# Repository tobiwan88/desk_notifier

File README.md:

# Desk notifier

A small desk display on an ESP32-S3. A round 240x240 GC9A01 screen turns through three animated pages: a clock with today's forecast for Munich, a cute squirrel that shows the indoor air quality from a BME688 sensor, and the squirrel's day at home, which follows the clock (coffee in the morning, laptop, lunch, reading, sleep). When the air gets bad the squirrel stays on screen and asks you to open a window until you press a button.

It started as the esp_eyes project (animated eyes on two displays) and was cut down to one display. The git history keeps the old work.

## What is in this repo
One repo holds the whole product: firmware, the custom board and the 3D-printed case.

| Part | Where | State |
|---|---|---|
| Firmware (ESP-IDF v6.1, C++23, host-tested core) | [`firmware/`](firmware/), [`docs/`](docs/) | Runs on the ESP32-S3 custom board (`DESK_BOARD_NOTIFIER_V1`) with a GC9A01, a BME688 and an SHT40; flashed and checked on a real board (sensors, display, Bluetooth setup). |
| Board `notifier-v1` (KiCad 10, 4 layers, 50 x 36 mm, JLCPCB assembly) | [`hardware/`](hardware/README.md) | Generated, routed and gate-checked, fab package builds. **Not ordered yet**: human review in KiCad, JLC placement preview and the display pinout check are still open ([`ORDER.md`](hardware/notifier-v1/ORDER.md)). |
| Case (Fusion, 3D printed PLA, two parts, snap-fit) | [`hardware/mechanics/`](hardware/mechanics/README.md) | First model with print files and a fit coupon. **Never printed.** |
| Helper tools (page previews, clip preparation) | [`tools/`](tools/), [`clipprep/`](clipprep/) | Used by the checks. |

## Limitations
Please read these before building one.
- **ESP32-S3 only.** The board uses an ESP32-S3-WROOM-1-N8R2, because C61 and C5 modules had no stock at JLCPCB. The earlier ESP32-C61 breadboard setup is no longer built or tested. The case is still untested (below).
- **The case is untested.** No part of it has been printed. The display module has no 3D model, so the pocket, window and plug alignment rest on assumed dimensions (header 2.54 mm, pin row 3.0 mm above the PCB edge, glass centre 26.5 mm above it, PCB plus glass 5.74 mm). Print `display_dummy.stl` and `coupon_m1.stl` first and compare. The SHT40 height (1.0 mm) is also an assumption. The cover needs one support and the USB-C collar may sit about 0.7 mm short of the connector.
- **Display orientation is unconfirmed.** The image is mirrored on X by default (`DESK_LCD_MIRROR_X`); flip it in menuconfig if your panel shows it backwards. The pin order of the display module on the board's socket is also still to be checked against a real module.
- **The air score is not BSEC.** It is a simple estimate from humidity and gas resistance and needs a few minutes of warm-up. The sensor reads a little warm next to the board, so indoor temperature is slightly high.
- **No firmware security by default.** The HTTP API, the pet page and OTA are open unless you set a token (`auth token`), the connection is plain HTTP, and the device is meant for a trusted home network. Do not expose it to the internet.
- **Weather and time need the internet** (Open-Meteo, SNTP). Without it the clock stays unset and the weather items disappear. The place defaults to Munich (change it with `POST /api/weather` or `weather at <lat> <lon>`), holidays are Bavarian, and the texts are English.
- **Pictures are stored but not shown** yet, there is one display, and the project is tuned to a single 240x240 round panel at 10 frames per second on a chip without an FPU.
- **The hardware generators overwrite KiCad edits.** Change `hardware/gen/*.py`, not the KiCad files, then re-run the pipeline. The router needs tools that `hardware/tools/setup_tools.sh` downloads, and its result differs between runs.
- **Development on macOS.** The scripts and notes assume macOS and a local ESP-IDF install in `~/esp/esp-idf`.

## What works today
- Rotating pages with fades, 10 frames per second. See [docs/pages.md](docs/pages.md).
- Five mascots, one per board (`idf.py menuconfig` → Desk notifier → Mascot): the squirrel, or a bunny, a stag, a lucky cat with her dog, or a penguin. The new ones have a home page (clock and air level) and a day page that follows their owner's week, and dress for the weather. The squirrel's extras (pet page, hearts, shop, visitors, plant) are add-ons with their own switches. See [docs/mascots.md](docs/mascots.md).
  - Clock: time (set over the internet), date, indoor and outdoor temperature, today's low, high and chance of rain.
  - Air: a squirrel mascot whose mood shows the air level (very good, good, okay, bad), with temperature, humidity and score.
  - Day: the squirrel at its desk at home, doing what fits the time and weekday. The room's climate changes it (stuffy air: it yawns or opens the window; too warm, too cold, too dry, too humid; a sudden smell), so does the weather (umbrella, cocoa, thunder), and special days decorate the room (birthday, anniversary, Christmas, Advent, Halloween, Oktoberfest, ...). The real weather shows in the window, the real time on the wall clock. The scene is never random, but little things are: blinks, glances, a wave, a bird on the windowsill, a ladybug on the desk, a shooting star, a paper plane, a rare golden acorn. The moon shows its real phase, rainbows follow rain, a window-sill plant grows with good air day after day, and a wall calendar counts down to birthdays.
  - Pet page at `http://<device>.local/pet`: feed it, have a coffee break or a party together, pet it, play, water the plant, say good night, give it gifts. Daily visits grow a friendship (five heart levels, never lost) with more reactions and visitors, and squirrel coins for the shop (six things a day: hats, places, things for the room, friends, seasonal specials); the squirrel picks its own outfit.
- Bad-air alert: the air page stays on, snoozed for 15 minutes by the button or by `POST /api/ack`. Without an alert the button shows the next page.
- Web page at `http://<device>.local/` and a small HTTP API.
- Wi-Fi, over-the-air updates, and a serial console.
- Picture upload (the clip format from esp_eyes) is stored but not shown yet.

Planned: pictures that stay on screen until acknowledged, Bosch BSEC2 for a proper IAQ value.

## What you need
Dev setup (works today), or the custom board in `hardware/` once it is built:
- ESP32-S3 board with 8 MB flash and PSRAM (the notifier-v1 board, or an S3 dev board with the same pins)
- GC9A01 round display, 240x240, SPI
- BME688 breakout (I2C)
- A push button (optional)
- USB cable

## The squirrel
The squirrel's mood follows the indoor air quality. What it wears follows the weather outside (Open-Meteo, Munich by default):

| Outside | Squirrel |
|---|---|
| below 8 °C | knitted hat and scarf |
| 25 °C or more | ice cream |
| sunny, daytime | sunglasses |
| drizzle, rain, thunder | umbrella |
| wind of 30 km/h or more | glides under the umbrella, tail streaming |

Items stack (cold, rainy and windy gives hat, umbrella and gliding). Preview every look on your computer with `uv run python tools/preview_pages.py out/` after `scripts/check.sh --quick`.

## Wiring
| Signal | GPIO | Note |
|---|---|---|
| Display SCL / SDA | 6 / 5 | |
| Display DC / RST / CS | 3 / 2 / 4 | |
| Display VCC / GND | 5V / GND | |
| BME688 SDA / SCL | 22 / 23 | 3V3, not 5V. Address 0x77 or 0x76, both are tried |
| Button | 24 | other leg to GND |

Details: [docs/wiring.md](docs/wiring.md). Pins can be changed in `idf.py menuconfig` under "Desk notifier".
If the picture is mirrored, flip `DESK_LCD_MIRROR_X` / `DESK_LCD_MIRROR_Y` there.

## Build and flash
You need ESP-IDF v6.1 and [uv](https://docs.astral.sh/uv/).

```sh
source scripts/idf-env.sh
cd firmware
idf.py -p /dev/cu.usbserial-XXXX flash monitor
```

## Connect to Wi-Fi
Open the serial console and run `wifi "<name>" <password>`. The device reboots and joins your network. It is then reachable as `desk-<last 6 MAC digits>.local`. The timezone is set in menuconfig (`DESK_TZ`, default Central Europe).

## API
By default the API needs no password (change with the console command `auth token`).

```sh
curl http://desk-xxxxxx.local/api/sensor     # temperature, humidity, pressure, gas, score
curl http://desk-xxxxxx.local/api/status     # uptime, memory, Wi-Fi, sensor state
curl -X POST http://desk-xxxxxx.local/api/ack   # snooze the alert
curl http://desk-xxxxxx.local/api/weather    # the last forecast
curl -X POST http://desk-xxxxxx.local/api/page -d '{"page":"day"}'   # clock, air, day or next ("weather" still works)
curl -X POST http://desk-xxxxxx.local/api/weather -d '{"lat":48.137,"lon":11.575,"place":"Munich"}'   # change the place
curl -X POST --data-binary @firmware.bin http://desk-xxxxxx.local/api/ota
```

## Console commands
`wifi`, `status`, `sensor`, `ack`, `page clock|air|day|next`, `weather [refresh | at <lat> <lon> [name]]`, `lcd pins`, `lcd init [hz]`, `hostname`, `auth open|token`, `token`, `reboot`, `factory-reset`.

## About the air-quality score
It is a simple estimate, not Bosch BSEC. 25 points come from humidity (best at 40 %) and 75 from the gas resistance compared with the highest value seen recently. It needs about 3 minutes to warm up and a stretch of clean air to be meaningful. The sensor also reads a little warm because it sits next to the board.

## For developers
`scripts/check.sh` runs the host tests (C++23, sanitizers), the Python tests and the firmware build. `--quick` skips the build. `uv run python tools/preview_pages.py` draws all pages as GIFs on your computer (after a host build). Pure logic lives in `firmware/components/*/core` and is tested on the PC. See [CLAUDE.md](CLAUDE.md) for the layout.

## Hardware and case
- Board: open `hardware/notifier-v1/notifier-v1.kicad_pro` with `hardware/open.sh`. Regenerate with `hardware/tools/pipeline_v1.sh`, check with `scripts/hw-check.sh`, order steps in [`hardware/notifier-v1/ORDER.md`](hardware/notifier-v1/ORDER.md), design notes in [`hardware/PLAN.md`](hardware/PLAN.md). Needs KiCad 10 (`source scripts/kicad-env.sh`).
- Case: print files and notes in [`hardware/mechanics/`](hardware/mechanics/README.md) (PLA, 0.2 mm layers, Bambu Lab plate included). Print the fit coupon first.
- Firmware: `idf.py build` in `firmware/` (target ESP32-S3). Wi-Fi, time zone and name can be set from a phone over Bluetooth: [`setup/`](setup/README.md).

## License
MIT. The BME68x driver in `firmware/components/sensor/third_party` is from Bosch Sensortec (BSD-3-Clause).

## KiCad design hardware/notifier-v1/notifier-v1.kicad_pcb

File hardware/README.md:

# Hardware: where to look

There is one KiCad project: **`notifier-v1/notifier-v1.kicad_pro`** (schematic + PCB).
Open it with `hardware/open.sh`, or File > Open Project in KiCad. Everything else is generated.

| What | Where |
|---|---|
| KiCad project (schematic, PCB) | `notifier-v1/` |
| Board profile (notes, rules the scripts check, datasheet cards) | `notifier-v1/BOARD.md`, `board.yaml`, `critical.yaml`, `parts/` |
| Order checklist, bring-up | `notifier-v1/ORDER.md` |
| Design notes, toolchain, lessons | `PLAN.md` |
| Review images (annotated renders, layers, 3D, schematic tiles) | `out/review/notifier-v1/` (after a pipeline run) |
| JLCPCB upload files (gerbers zip, BOM, CPL) | `out/fab/notifier-v1/` (after a pipeline run) |
| Router logs | `out/route/` |
| Board-neutral checks (critical blocks, regulator, impedance) | `calc/` (each takes the board folder) |
| Generators (edit these, not the KiCad files) | `gen/notifier_v1.py` (schematic), `gen/layout_v1.py` (placement) |

The KiCad files are regenerated by `tools/pipeline_v1.sh`: edits made in KiCad are overwritten on the
next run. Review in KiCad, then change the generators. `out/` is not in git; `tools/setup_tools.sh`
installs the routers once.

Agent skills (board-neutral): `hw-base` (read first), `kicad-schematic`, `kicad-layout`, `hw-parts` in `.claude/skills/`.

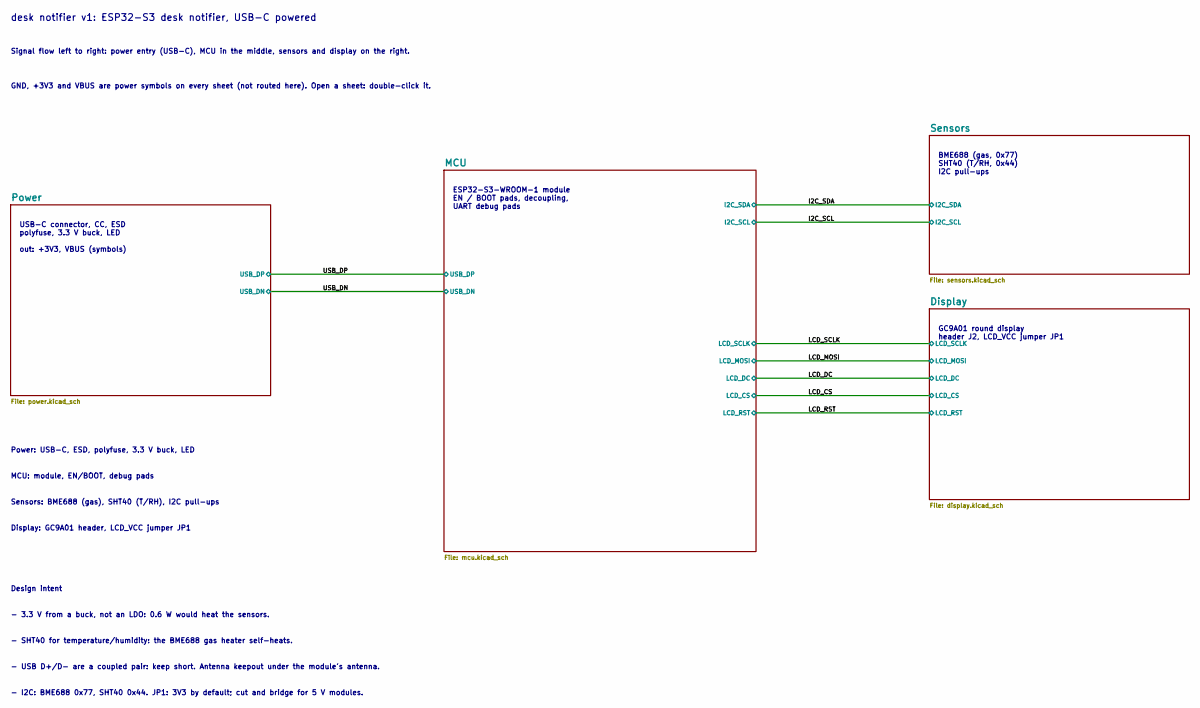
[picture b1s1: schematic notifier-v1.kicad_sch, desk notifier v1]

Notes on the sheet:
USB-C connector, CC, ESD polyfuse, 3.3 V buck, LED out: +3V3, VBUS (symbols)
ESP32-S3-WROOM-1 module EN / BOOT pads, decoupling, UART debug pads
Design intent
- 3.3 V from a buck, not an LDO: 0.6 W would heat the sensors.
MCU: module, EN/BOOT, debug pads
Power: USB-C, ESD, polyfuse, 3.3 V buck, LED
Signal flow left to right: power entry (USB-C), MCU in the middle, sensors and display on the right.
- USB D+/D- are a coupled pair: keep short. Antenna keepout under the module's antenna.
desk notifier v1: ESP32-S3 desk notifier, USB-C powered
GND, +3V3 and VBUS are power symbols on every sheet (not routed here). Open a sheet: double-click it.
- I2C: BME688 0x77, SHT40 0x44. JP1: 3V3 by default; cut and bridge for 5 V modules.
GC9A01 round display header J2, LCD_VCC jumper JP1
Display: GC9A01 header, LCD_VCC jumper JP1
BME688 (gas, 0x77) SHT40 (T/RH, 0x44) I2C pull-ups
Sensors: BME688 (gas), SHT40 (T/RH), I2C pull-ups
- SHT40 for temperature/humidity: the BME688 gas heater self-heats.

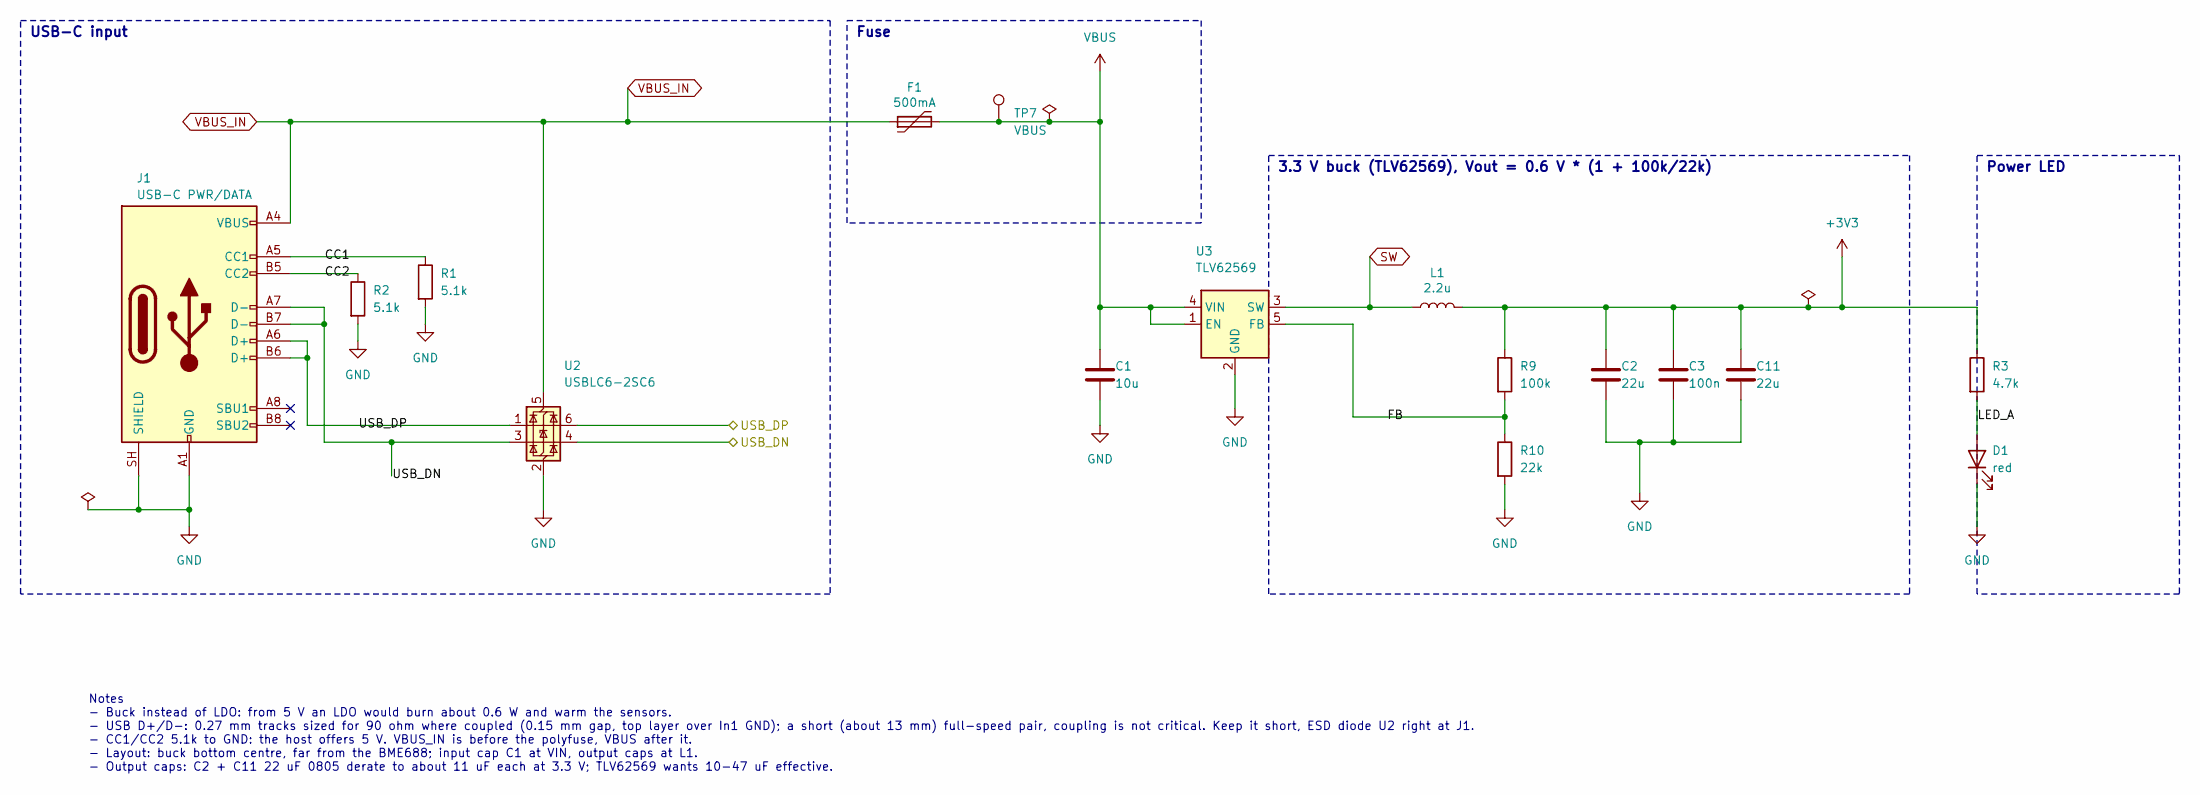
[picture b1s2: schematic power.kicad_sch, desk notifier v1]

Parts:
C1: 10u; C_0603_1608Metric; LCSC C19702
C2, C11: 22u; C_0805_2012Metric; LCSC C45783
C3: 100n; C_0402_1005Metric; LCSC C1525
D1: red; LED_0603_1608Metric; LCSC C2286
F1: 500mA; Fuse_1206_3216Metric; LCSC C70077
J1: USB-C PWR/DATA; USB_C_Receptacle_HRO_TYPE-C-31-M-12; LCSC C165948
L1: 2.2u; L_Cenker_CKCS4030; LCSC C354584
R1, R2: 5.1k; R_0402_1005Metric; LCSC C25905
R3: 4.7k; R_0402_1005Metric; LCSC C25900
R9: 100k; R_0402_1005Metric; LCSC C25741
R10: 22k; R_0402_1005Metric; LCSC C25768
TP7: VBUS; TestPoint_Pad_D1.0mm
U2: USBLC6-2SC6; SOT-23-6; LCSC C7519
U3: TLV62569; SOT-23-5; LCSC C141836

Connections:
+3V3: C2.1, C3.1, C11.1, L1.2, R3.1, R9.1; also elsewhere on the board
/Power/CC1: J1.A5 (CC1), R1.1
/Power/CC2: J1.B5 (CC2), R2.1
/Power/FB: R9.2, R10.1, U3.5 (FB)
/Power/LED_A: D1.2 (A), R3.2
/USB_DN: J1.A7 (D-), J1.B7 (D-), U2.3 (I/O2), U2.4 (I/O2); also elsewhere on the board
/USB_DP: J1.A6 (D+), J1.B6 (D+), U2.1 (I/O1), U2.6 (I/O1); also elsewhere on the board
GND: C1.2, C2.2, C3.2, C11.2, D1.1 (K), J1.A1 (GND), J1.A12 (GND), J1.B1 (GND), J1.B12 (GND), J1.SH (SHIELD), R1.2, R2.2, R10.2, U2.2 (GND), U3.2 (GND); also elsewhere on the board
SW: L1.1, U3.3 (SW)
VBUS: C1.1, F1.2, TP7.1, U3.1 (EN), U3.4 (VIN); also elsewhere on the board
VBUS_IN: F1.1, J1.A4 (VBUS), J1.A9 (VBUS), J1.B4 (VBUS), J1.B9 (VBUS), U2.5 (VBUS)

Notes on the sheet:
3.3 V buck (TLV62569), Vout = 0.6 V * (1 + 100k/22k)
USB-C input
Notes - Buck instead of LDO: from 5 V an LDO would burn about 0.6 W and warm the sensors. - USB D+/D-: 0.27 mm tracks sized for 90 ohm where coupled (0.15 mm gap, top layer over In1 GND); a short (about 13 mm) full-speed pair, coupling is not critical. Keep it short, ESD diode U2 right at J1. - CC1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
Power LED
Fuse

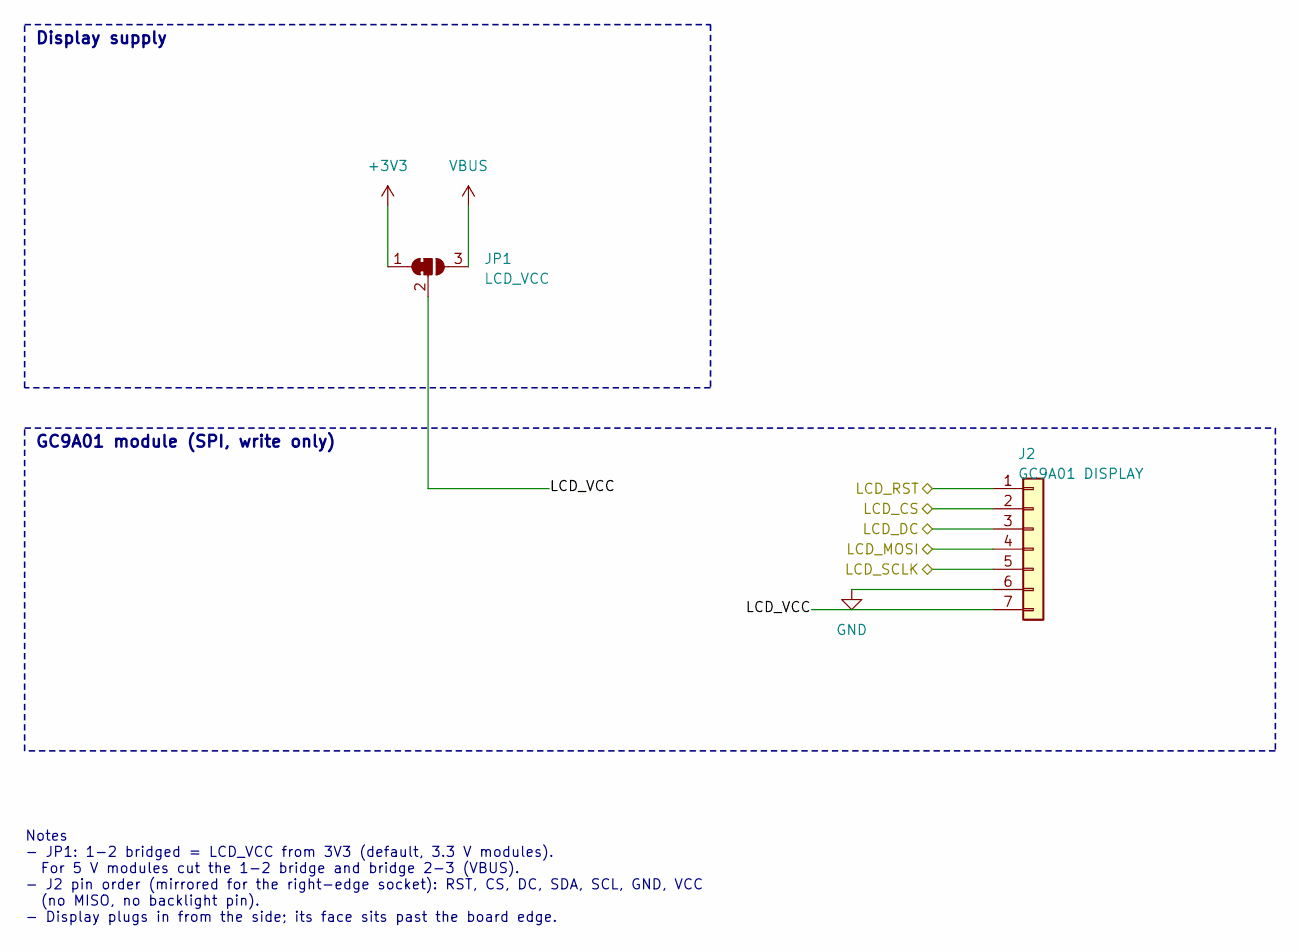
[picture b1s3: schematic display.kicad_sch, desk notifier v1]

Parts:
J2: GC9A01 DISPLAY; PinSocket_1x07_P2.54mm_Horizontal; LCSC C22436148
JP1: LCD_VCC; SolderJumper-3_P1.3mm_Bridged12_RoundedPad1.0x1.5mm

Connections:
+3V3: JP1.1 (A); also elsewhere on the board
/Display/LCD_VCC: J2.7, JP1.2 (C)
/LCD_CS: J2.2; also elsewhere on the board
/LCD_DC: J2.3; also elsewhere on the board
/LCD_MOSI: J2.4; also elsewhere on the board
/LCD_RST: J2.1; also elsewhere on the board
/LCD_SCLK: J2.5; also elsewhere on the board
GND: J2.6; also elsewhere on the board
VBUS: JP1.3 (B); also elsewhere on the board

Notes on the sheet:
Display supply
GC9A01 module (SPI, write only)
Notes - JP1: 1-2 bridged = LCD_VCC from 3V3 (default, 3.3 V modules). For 5 V modules cut the 1-2 bridge and bridge 2-3 (VBUS). - J2 pin order (mirrored for the right-edge socket): RST, CS, DC, SDA, SCL, GND, VCC (no MISO, no backlight pin). - Display plugs in from the side; its face sits past the 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

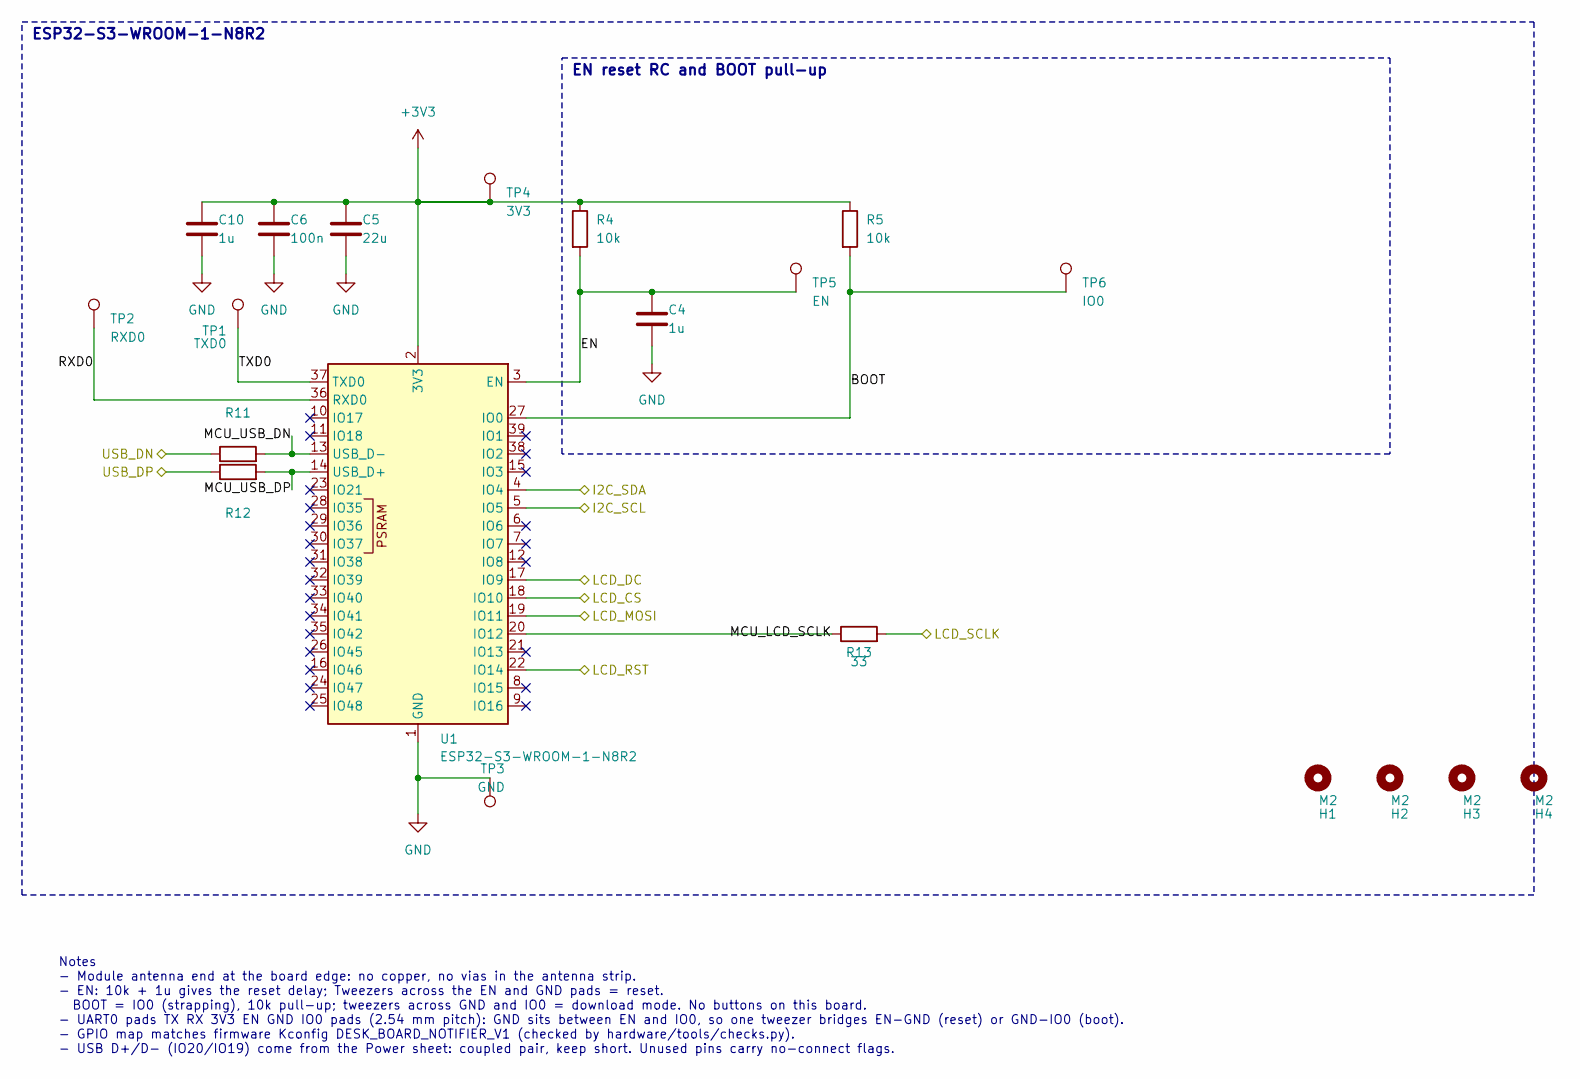
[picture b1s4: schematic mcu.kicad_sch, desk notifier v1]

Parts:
C4, C10: 1u; C_0402_1005Metric; LCSC C52923
C5: 22u; C_0805_2012Metric; LCSC C45783
C6: 100n; C_0402_1005Metric; LCSC C1525
H1, H2, H3, H4: M2; MountingHole_2.2mm_M2
R4, R5: 10k; R_0402_1005Metric; LCSC C25744
R11, R12: 22; R_0402_1005Metric; LCSC C25092
R13: 33; R_0402_1005Metric; LCSC C25105
TP1: TXD0; TestPoint_Pad_D1.5mm
TP2: RXD0; TestPoint_Pad_D1.5mm
TP3: GND; TestPoint_Pad_D1.5mm
TP4: 3V3; TestPoint_Pad_D1.5mm
TP5: EN; TestPoint_Pad_D1.5mm
TP6: IO0; TestPoint_Pad_D1.5mm
U1: ESP32-S3-WROOM-1-N8R2; ESP32-S3-WROOM-1; LCSC C2913204

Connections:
+3V3: C5.1, C6.1, C10.1, R4.1, R5.1, TP4.1, U1.2 (3V3); also elsewhere on the board
/I2C_SCL: U1.5 (IO5); also elsewhere on the board
/I2C_SDA: U1.4 (IO4); also elsewhere on the board
/LCD_CS: U1.18 (IO10); also elsewhere on the board
/LCD_DC: U1.17 (IO9); also elsewhere on the board
/LCD_MOSI: U1.19 (IO11); also elsewhere on the board
/LCD_RST: U1.22 (IO14); also elsewhere on the board
/LCD_SCLK: R13.2; also elsewhere on the board
/MCU/BOOT: R5.2, TP6.1, U1.27 (IO0)
/MCU/EN: C4.1, R4.2, TP5.1, U1.3 (EN)
/MCU/MCU_LCD_SCLK: R13.1, U1.20 (IO12)
/MCU/MCU_USB_DN: R11.2, U1.13 (USB_D-)
/MCU/MCU_USB_DP: R12.2, U1.14 (USB_D+)
/MCU/RXD0: TP2.1, U1.36 (RXD0)
/MCU/TXD0: TP1.1, U1.37 (TXD0)
/USB_DN: R11.1; also elsewhere on the board
/USB_DP: R12.1; also elsewhere on the board
GND: C4.2, C5.2, C6.2, C10.2, TP3.1, U1.1 (GND), U1.40 (GND), U1.41 (GND); also elsewhere on the board

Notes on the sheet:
ESP32-S3-WROOM-1-N8R2
EN reset RC and BOOT pull-up
Notes - Module antenna end at the board edge: no copper, no vias in the antenna strip. - EN: 10k + 1u gives the reset delay; Tweezers across the EN and GND pads = reset. BOOT = IO0 (strapping), 10k pull-up; tweezers across GND and IO0 = download mode. No buttons on this board. - UART0 pads TX RX 3V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

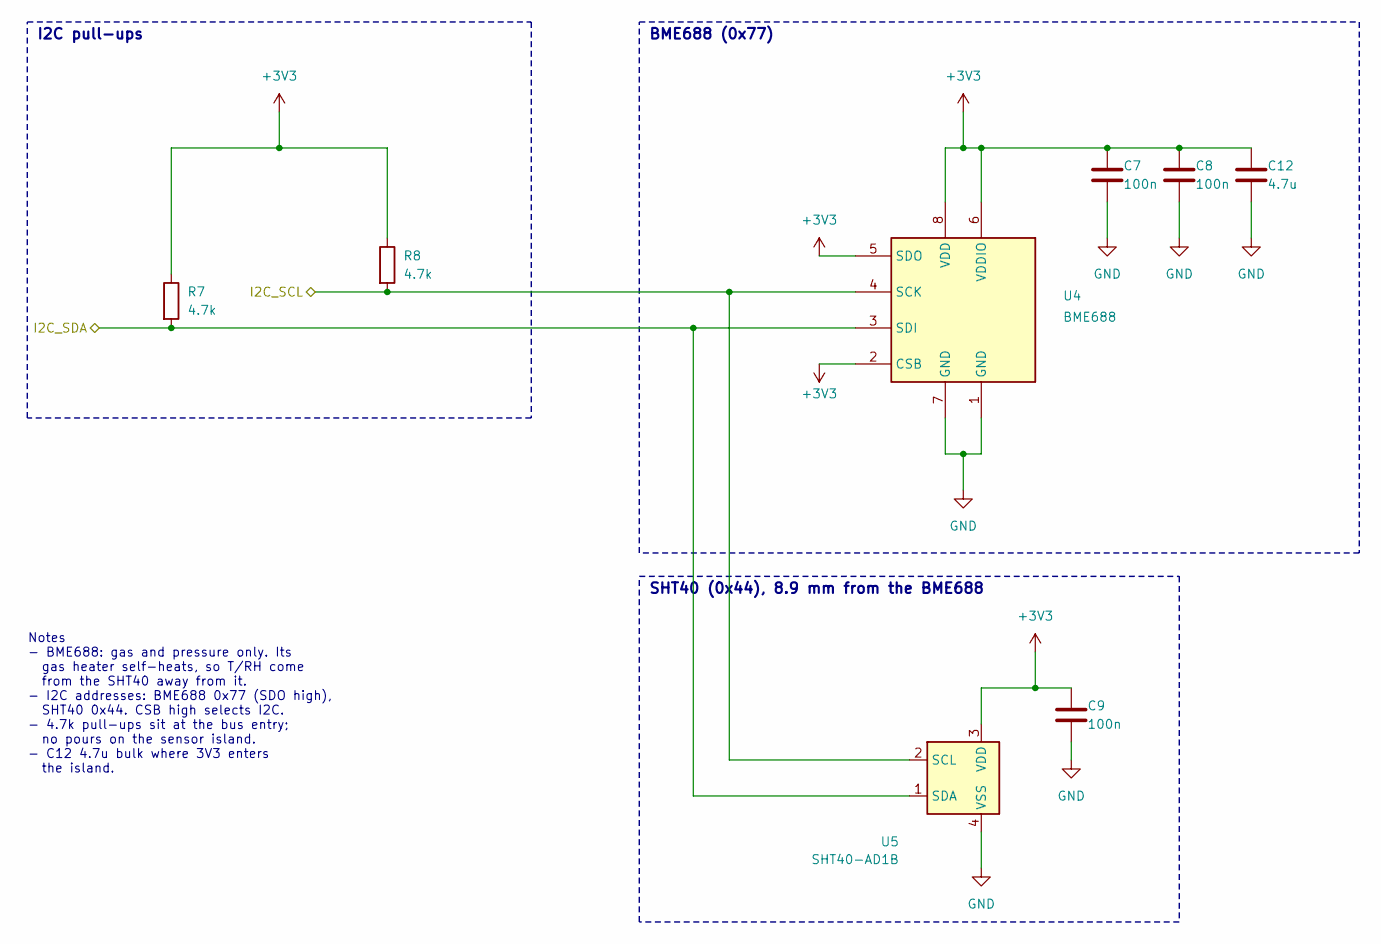
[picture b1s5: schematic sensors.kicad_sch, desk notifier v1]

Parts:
C7, C8, C9: 100n; C_0402_1005Metric; LCSC C1525
C12: 4.7u; C_0603_1608Metric; LCSC C19666
R7, R8: 4.7k; R_0402_1005Metric; LCSC C25900
U4: BME688; Bosch_LGA-8_3x3mm_P0.8mm_ClockwisePinNumbering; LCSC C3664478
U5: SHT40-AD1B; Sensirion_DFN-4_1.5x1.5mm_P0.8mm_SHT4x_NoCentralPad; LCSC C2909890

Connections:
+3V3: C7.1, C8.1, C9.1, C12.1, R7.1, R8.1, U4.2 (CSB), U4.5 (SDO), U4.6 (VDDIO), U4.8 (VDD), U5.3 (VDD); also elsewhere on the board
/I2C_SCL: R8.2, U4.4 (SCK), U5.2 (SCL); also elsewhere on the board
/I2C_SDA: R7.2, U4.3 (SDI), U5.1 (SDA); also elsewhere on the board
GND: C7.2, C8.2, C9.2, C12.2, U4.1 (GND), U4.7 (GND), U5.4 (VSS); also elsewhere on the board

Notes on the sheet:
SHT40 (0x44), 8.9 mm from the BME688
Notes - BME688: gas and pressure only. Its gas heater self-heats, so T/RH come from the SHT40 away from it. - I2C addresses: BME688 0x77 (SDO high), SHT40 0x44. CSB high selects I2C. - 4.7k pull-ups sit at the bus entry; no pours on the sensor island. - C12 4.7u bulk where 3V3 enters the island.
BME688 (0x77)
I2C pull-ups

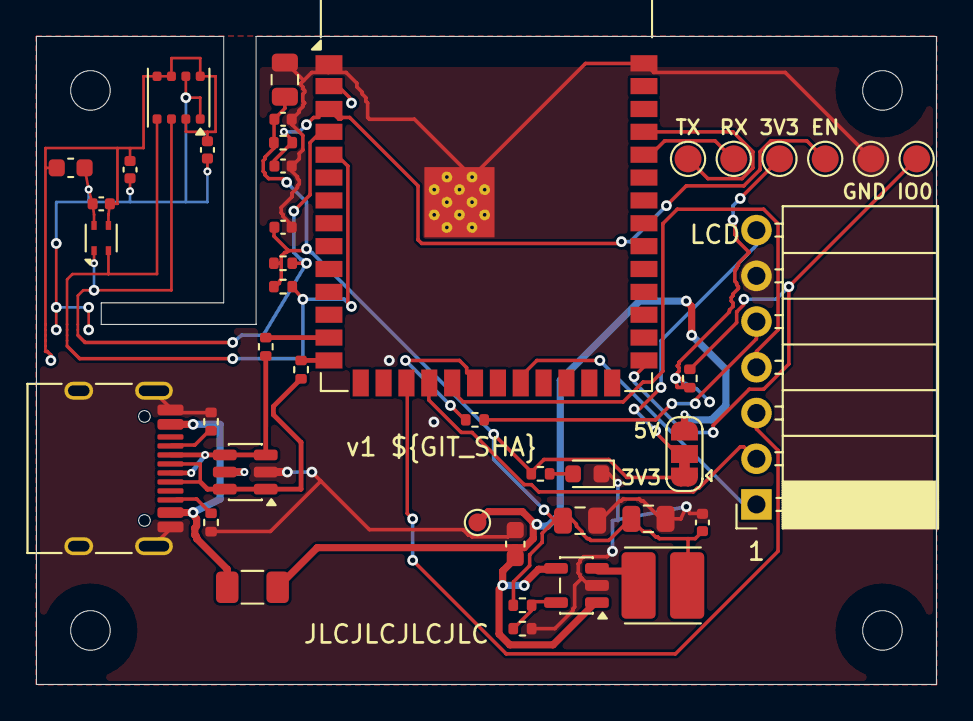
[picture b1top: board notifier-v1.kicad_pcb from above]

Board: 4 copper layers, 50.0 x 36.0 mm, 46 parts (0 on the bottom side), 26 nets.

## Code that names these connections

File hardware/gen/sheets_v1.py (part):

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x to the right, y down. Signal flow runs left to right, positive rails up, GND down.

Net naming in KiCad terms: GND, +3V3, VBUS are power symbols (global); VBUS_IN and SW are global
labels (routing patterns refer to them); USB_DP/USB_DN, I2C_* and LCD_* cross sheets through
hierarchical pins and a local label on the root page ("/USB_DP", ...); the rest is local to its
sheet ("/MCU/EN", "/Power/CC1", ...).
"""

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    s.tag("J1", (-8, -22), (-8, -19.5))
    s.wire(("J1", "A4"), (26, 28), ("F1", "1"))               # VBUS_IN rail
    s.wire((26, 28), (24, 28))
    s.label("VBUS_IN", 24, 28, 180, "global")
    s.wire(("U2", "5"), (41, 28))
    s.wire((46, 28), (46, 26))
    s.label("VBUS_IN", 46, 26, 0, "global")                   # second label: a global label must appear twice
    s.part("R1", 34, 37.5)                                    # 5.1k CC pull-downs: sink identification
    s.wire(("J1", "A5"), ("R1", "1"))
    s.label("CC1", 28, 36, 0)
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    s.wire((28, 39), (28, 47), ("U2", "3"))
    s.part("U2", 41, 46)                                      # ESD diode in line with the data pair
    s.tag("U2", (3, -9), (3, -6.5))
    s.label("USB_DP", 30, 46, 0)
    s.wire((32, 47), (32, 49))
    s.label("USB_DN", 32, 49, 0)
    s.wire(("U2", "2"), (41, 51))
    s.power("GND", 41, 51)
    s.wire(("U2", "6"), (52, 46))
    s.label("USB_DP", 52, 46, 0, "hier")
    s.wire(("U2", "4"), (52, 47))
    s.label("USB_DN", 52, 47, 0, "hier")
    s.wire(("J1", "A1"), (20, 52))                            # GND (A1, A12, B1, B12 share one pin point), shield
    s.power("GND", 20, 52)
    s.wire(("J1", "SH"), (17, 51), (20, 51))
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    s.part("D1", 112 + b, 48, 90)
    s.wire(("R3", "1"), (112 + b, 39))
    s.wire(("R3", "2"), ("D1", "2"))
    s.label("LED_A", 112 + b, 45.5, 0)
    s.wire(("D1", "1"), (112 + b, 52))
    s.power("GND", 112 + b, 52)
    s.text(14, 62, "Notes\n"
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    s.wire((80, 68), (84, 68))
    s.part("TP3", 84, 68, 180)
    # USB data and UART pads on the left
    for ref, pin, net, y, up in (("R11", "13", "USB_DN", 50, True), ("R12", "14", "USB_DP", 51, False)):
        s.part(ref, 70, y, 90)                                # 22 ohm series resistors at the module pins
        a, b_ = s.at(ref, "1"), s.at(ref, "2")
        left, right = ("1", "2") if a[0] < b_[0] else ("2", "1")
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    s.label("RXD0", 62, 45, 180)
    s.part("TP2", 62, 43)
    # I2C and display bus on the right
    for pin, net, y in (("4", "I2C_SDA", 52), ("5", "I2C_SCL", 53)):
        s.wire(("U1", pin), (89, y))
        s.label(net, 89, y, 0, "hier")
    s.part("R13", 104.5, 60, 90)                              # 33 ohm series termination on the display clock
    assert s.at("R13", "1")[0] < s.at("R13", "2")[0], "R13 pin 1 must face the module"
    s.wire(("U1", "20"), ("R13", "1"))
    s.label("MCU_LCD_SCLK", *(v / 2.54 for v in s.at("R13", "1")), 180)  # at() is in mm, labels in cells
    xr = s.at("R13", "2")[0] / 2.54 + 2
    s.wire(("R13", "2"), (xr, 60))
    s.label("LCD_SCLK", xr, 60, 0, "hier")
    s.tag("R13", (0, 2.6), (0, 3.9), just="center")
    for pin, net, y in (("19", "LCD_MOSI", 59), ("17", "LCD_DC", 57), ("18", "LCD_CS", 58), ("22", "LCD_RST", 62)):
        s.wire(("U1", pin), (89, y))
        s.label(net, 89, y, 0, "hier")
    # EN: pull-up, RC delay cap, reset button, test pad
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    s.frame(8, 14, 36, 36, "I2C pull-ups")
    s.wire((12, 31), (16, 31), (45, 31))
    s.wire(("U4", "3"), (45, 31))
    s.label("I2C_SDA", 12, 31, 180, "hier")
    s.wire((24, 29), (47, 29))
    s.wire(("U4", "4"), (47, 29))
    s.label("I2C_SCL", 24, 29, 180, "hier")
    s.part("R7", 16, 29.5)
    s.part("R8", 28, 27.5)
    s.wire(("R7", "1"), (16, 21), (28, 21))
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    s.wire(("JP1", "3"), (32, 19))
    s.power("VBUS", 32, 19)
    s.wire(("JP1", "2"), (30, 33), (36, 33))
    s.label("LCD_VCC", 36, 33, 0)
    s.frame(10, 30, 72, 46, "GC9A01 module (SPI, write only)")
    s.part("J2", 60, 36)
    y7 = s.at("J2", "7")[1] / 2.54
    s.wire(("J2", "7"), (49, y7))
    s.label("LCD_VCC", 49, y7, 180)
    s.tag("J2", (-2, -12), (-2, -9.5))
    y6 = s.at("J2", "6")[1] / 2.54
    s.wire(("J2", "6"), (51, y6))
    s.power("GND", 51, y6)
    for pin, net in zip("12345", ("LCD_RST", "LCD_CS", "LCD_DC", "LCD_MOSI", "LCD_SCLK")):
        y = s.at("J2", pin)[1] / 2.54
        s.wire(("J2", pin), (55, y))
        s.label(net, 55, y, 180, "hier")
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    root_uuid = str(uuid.uuid5(uuid.NAMESPACE_URL, "root"))
    sd = [
        dict(name="Power", file=SHEET_FILES["Power"], x=14, y=30, w=30, h=22, page="2", uuid=SHEET_UUID["Power"],
             pins=[("right", 38, "USB_DP"), ("right", 40, "USB_DN")]),
        dict(name="MCU", file=SHEET_FILES["MCU"], x=64, y=26, w=36, h=44, page="3", uuid=SHEET_UUID["MCU"],
             pins=[("left", 38, "USB_DP"), ("left", 40, "USB_DN"), ("right", 30, "I2C_SDA"), ("right", 32, "I2C_SCL")]
             + [("right", 46 + 2 * i, n) for i, n in enumerate(LCD)]),
        dict(name="Sensors", file=SHEET_FILES["Sensors"], x=120, y=22, w=30, h=16, page="4", uuid=SHEET_UUID["Sensors"],
             pins=[("left", 30, "I2C_SDA"), ("left", 32, "I2C_SCL")]),
        dict(name="Display", file=SHEET_FILES["Display"], x=120, y=42, w=30, h=22, page="5", uuid=SHEET_UUID["Display"],
             pins=[("left", 46 + 2 * i, n) for i, n in enumerate(LCD)]),
    ]
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
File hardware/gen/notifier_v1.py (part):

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    "C10": ("Device:C", "1u", C0402, "C52923", "MCU", 0),
    # USB D+/D- series resistors, 22 ohm, close to the module pins: Espressif schematic checklist, section "USB"
    # (same URL): "series resistors of 22 to 33 ohm" on D+/D-. UNI-ROYAL 0402WGF220JTCE, 1 %, Basic.
    "R11": ("Device:R", "22", R0402, "C25092", "MCU", 0),   # USB_DN -> MCU_USB_DN (module pin 13)
    "R12": ("Device:R", "22", R0402, "C25092", "MCU", 0),   # USB_DP -> MCU_USB_DP (module pin 14)
    "R13": ("Device:R", "33", R0402, "C25105", "MCU", 0),   # LCD SCLK series termination at module pin 20
    "R4": ("Device:R", "10k", R0402, "C25744", "MCU", 0),
    "C4": ("Device:C", "1u", C0402, "C52923", "MCU", 0),
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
